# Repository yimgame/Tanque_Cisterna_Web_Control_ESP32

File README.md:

# Control de bomba para tanque con cisterna por ESP32

Proyecto para controlar una bomba con una ESP32, dos sensores ultrasónicos y un relé. El sistema publica una interfaz web en la propia placa para ver el estado del tanque y la cisterna, habilitar control manual, cambiar el WiFi y acceder por IP o por mDNS.

## Qué incluye

- Servidor web local en la ESP32.
- Medición de cisterna y tanque en tiempo real.
- Modo automático con lógica de llenado.
- Arranque manual con modal de confirmación.
- Arranque manual directo del relé (independiente de niveles), con corte por tiempo máximo.
- Cambio de credenciales WiFi desde ruta oculta de configuración.
- Ruta `/log` con bitácora de acciones (IP, fecha/hora cuando hay NTP).
- Histograma de consumo de agua estimado por hora.
- Acceso por IP local y por `http://tanque.local/`.

## Materiales

- 1 ESP32 compatible, por ejemplo NodeMCU 32S.
- 2 sensores ultrasónicos.
- 1 relé para la bomba.
- Fuente y cableado adecuados para tu instalación.

## Requisitos

1. Instala y abre **[Arduino IDE](https://docs.arduino.cc/software/ide/)**.
2. Configura el soporte de ESP32 en el IDE.
3. Si tu placa no comunica, instala el driver correcto, por ejemplo **[WCH CH340 Driver](https://www.tecneu.com/blogs/tutoriales-de-electronica/guia-paso-a-paso-para-instalar-el-driver-ch340g-en-windows-y-mac?srsltid=AfmBOorWYHYStt433QoR3n1FMt2kGe9WqyiUDfcd9x9y8EoXX6WNAXF_)** o **[Silicon Labs CP210x](https://community.silabs.com/s/question/0D58Y00008K88dCSAR/how-to-download-cp210x-usb-to-uart-bridge-vcp-drivers?language=es)**.
4. Asegúrate de tener las librerías necesarias para ESP32 y WiFiManager.

## Uso

1. Abre el proyecto en Arduino IDE.
2. Compila y sube el sketch que está en [sketch/sketch.ino](sketch/sketch.ino).
3. La primera vez, la ESP32 abrirá el portal de WiFiManager para conectar a tu red.
4. Una vez conectada, revisa el monitor serie: ahí verás la IP local y la URL de acceso.
5. También puedes entrar desde la web con la IP mostrada o con `http://tanque.local/` si tu red resuelve mDNS.

## Prueba rápida

- En el simulador de Wokwi puedes probar la lógica y mover los sensores.
- Proyecto de referencia: https://wokwi.com/projects/467575637641711617

## Nota sobre red

La interfaz web ya no depende de editar manualmente `ssid` y `password`. La red se gestiona con WiFiManager.

Para cambiar credenciales guardadas, entra a la ruta oculta `http://tanque.local/config` (o `http://IP_LOCAL/config`) y usa la opción **CAMBIAR WIFI**.

En esa misma pantalla también puedes guardar la configuración de control del sistema:

- Diámetro y altura de tanque y cisterna.
- Caudal de la bomba en L/min.
- Distancia de lleno y vacío para tanque y cisterna.
- Distancia actual medida por cada sensor.

El sketch calcula la capacidad de cada depósito a partir de diámetro y altura, y usa la calibración de distancias para determinar los arranques y paradas.

En esa misma ruta `/config` tienes el acceso a **VER LOG**, que abre `http://tanque.local/log`.

La conexión queda en DHCP por defecto para que el autoconectado sea más estable, pero ahora también puedes cargar IP manual desde el mismo portal.

### Modo simultáneo: DHCP + IP manual

En el portal de WiFiManager verás los campos de IP, gateway, máscara y DNS.

1. Si dejas esos campos vacíos, la ESP32 conecta por DHCP (automático).
2. Si completas esos campos, la ESP32 conecta con IP manual (estática).

### Opcional avanzado: IP manual por código

Si prefieres dejar fija la IP desde el código, el sketch también está preparado con un ejemplo.

1. Abre [sketch/sketch.ino](sketch/sketch.ino).
2. Busca el bloque `CONFIGURACIÓN DE IP MANUAL (ESTÁTICA)`.
3. Descomenta estas 4 líneas y ajusta los valores a tu red:
	- `IP_MANUAL(192, 168, 0, 34)`
	- `GW_MANUAL(192, 168, 0, 1)`
	- `MASK_MANUAL(255, 255, 255, 0)`
	- `DNS_MANUAL(8, 8, 8, 8)`
4. En `setup()`, descomenta esta línea:
	- `wifiManager.setSTAStaticIPConfig(IP_MANUAL, GW_MANUAL, MASK_MANUAL, DNS_MANUAL);`
5. Compila y vuelve a subir el sketch.

Si dejas todo comentado, seguirá usando el modo simultáneo del portal (DHCP por defecto con opción manual).

## Control manual y seguridad

1. El botón **ARRANQUE** muestra un modal de advertencia antes de activar el relé.
2. Al confirmar, el relé puede encender en modo manual directo (salta la lógica automática de niveles).
3. El botón **PARADA** corta el relé manual.
4. El botón **AUTO / RESET** vuelve al modo automático.
5. El límite de seguridad de 10 minutos sigue activo incluso en modo manual directo.

## Logs y consumo

1. Entra a `http://tanque.local/config`.
2. Abre **VER LOG** para ir a `http://tanque.local/log`.
3. Allí verás la bitácora de comandos con acción, IP cliente y marca de tiempo.
4. También verás un histograma de consumo estimado (L/h), calculado por variación del tanque.
5. Si no hay hora sincronizada por red, la marca de tiempo se guarda como uptime.

## Primera conexión

1. Conéctate desde el celular o PC a la red WiFi que levanta la ESP32 (portal de WiFiManager).
2. Elige tu red WiFi de casa y escribe la contraseña.
3. Guarda y sal del portal. La red temporal de la ESP32 se cierra.
4. Vuelve a conectarte a tu red normal y entra a `http://tanque.local` o a la IP mostrada por el monitor serie.

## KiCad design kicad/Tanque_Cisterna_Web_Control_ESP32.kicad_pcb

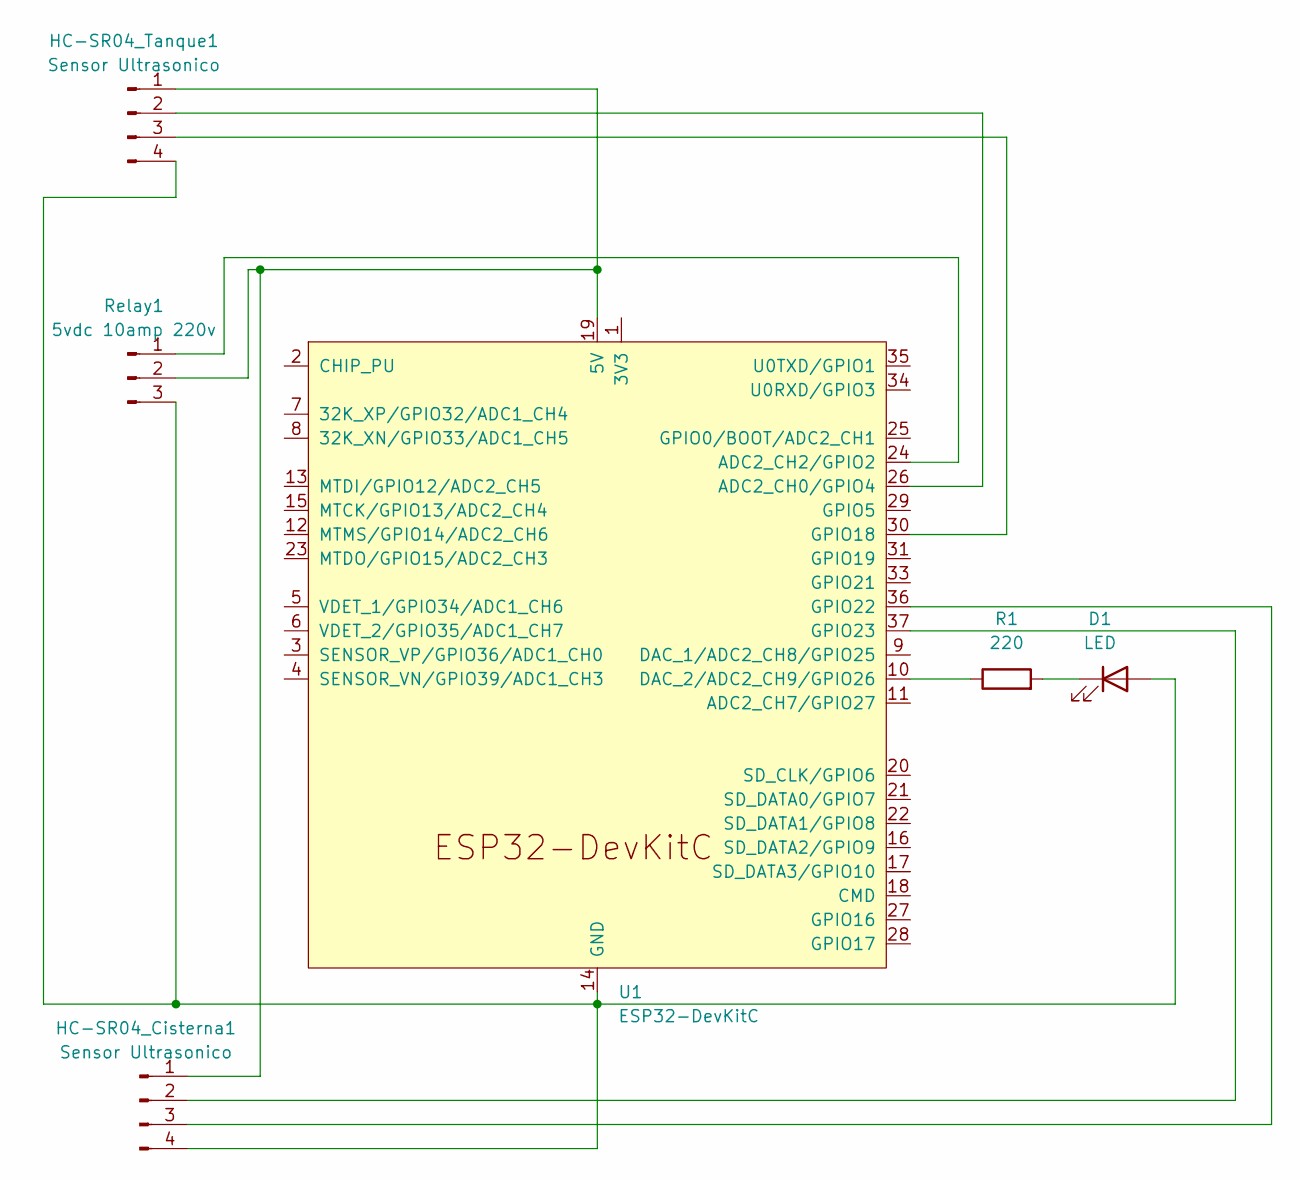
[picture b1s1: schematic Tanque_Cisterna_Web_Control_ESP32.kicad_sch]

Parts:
D1: LED; LED_D5.0mm
HC-SR04_Cisterna1, HC-SR04_Tanque1: Sensor Ultrasonico; PinSocket_1x04_P2.54mm_Vertical
R1: 220; R_Axial_DIN0207_L6.3mm_D2.5mm_P7.62mm_Horizontal
Relay1: 5vdc 10amp 220v; PinSocket_1x03_P2.54mm_Vertical
U1: ESP32-DevKitC

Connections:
unnamed: D1.2 (A), HC-SR04_Cisterna1.4, HC-SR04_Tanque1.4, Relay1.3, U1.14 (GND), U1.32 (GND), U1.38 (GND)
unnamed: D1.1 (K), R1.2
unnamed: HC-SR04_Cisterna1.1, HC-SR04_Tanque1.1, Relay1.2, U1.19 (5V)
unnamed: HC-SR04_Cisterna1.2, U1.37 (GPIO23)
unnamed: HC-SR04_Cisterna1.3, U1.36 (GPIO22)
unnamed: HC-SR04_Tanque1.2, U1.26 (ADC2_CH0/GPIO4)
unnamed: HC-SR04_Tanque1.3, U1.30 (GPIO18)
unnamed: Relay1.1, U1.24 (ADC2_CH2/GPIO2)
unnamed: R1.1, U1.10 (DAC_2/ADC2_CH9/GPIO26)

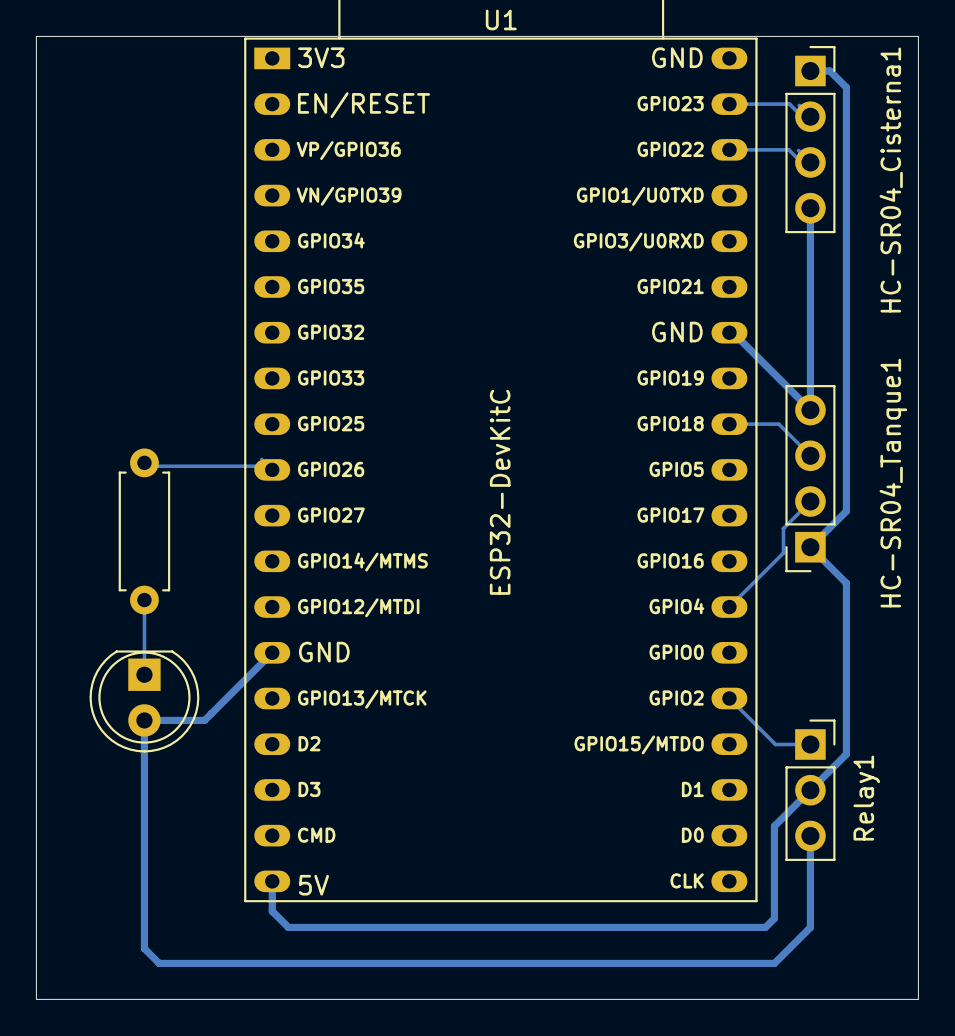
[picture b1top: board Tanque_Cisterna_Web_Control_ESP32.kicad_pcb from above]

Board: 2 copper layers, 49.0 x 53.5 mm, 6 parts (0 on the bottom side), 9 nets.

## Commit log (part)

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2026-06-23 Tanque Cisterna primer commit, codigo testeado en simulador wokwi y en la ESP32 hardware
    https://wokwi.com/projects/467575637641711617
2026-06-23 Just Coding 4 Fun !!!
2026-06-23 Revise ESP32 setup instructions in README
    Updated instructions for setting up ESP32 with Arduino IDE, including driver installation and WiFi configuration.
2026-06-23 Revise README title and project description
    Updated project title and description in README.
2026-06-23 Revise README setup instructions for ESP32 project
    Updated setup instructions and improved clarity.
2026-06-23 Update project title and description in README
2026-06-23 Rename image-1.png to app.png
2026-06-23 Rename image-2.png to arduino-run.png
2026-06-23 Rename image.png to wokwi-simulator.png
2026-06-23 Update images in README.md
    image links update
2026-06-23 Fix typo in README.md
2026-06-24 Fix typo in sensor description in README.md
2026-06-27 Se agregaron botones de encendido parada, ahora calcula los litros tanque 1000 cistrerna 500 litros, tiene un timer de funcionamioento por tiempo que para a los 10 min segun los 33 litros por min de 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
2026-06-27 Nueva app web con hostname http://tanque.local se agregaron botones de arranque parada, timer de funcionamiento 10 min para 500 litros con una centrifuga bomba de 33 l/m y datos de capacidad aprox pa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
2026-06-28 Corrección de la logica de arranque manual, detalle de tamaño de botones parejos.
